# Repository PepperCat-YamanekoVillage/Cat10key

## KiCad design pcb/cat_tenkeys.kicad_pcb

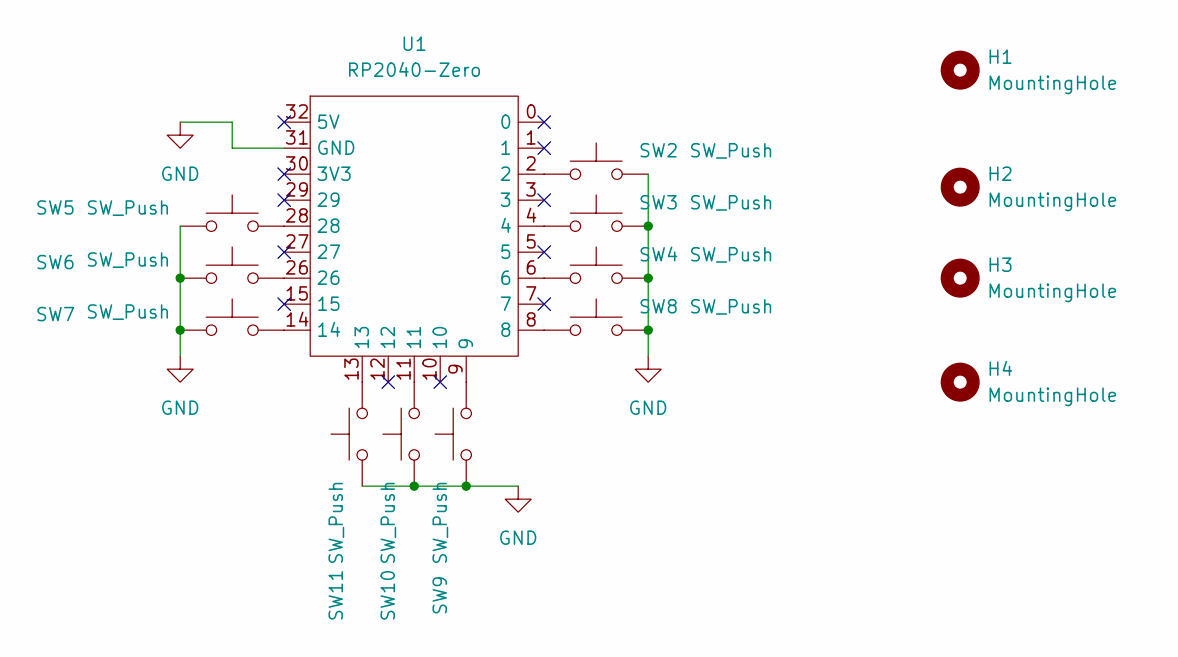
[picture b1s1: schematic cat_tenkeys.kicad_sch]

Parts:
H1, H2, H3, H4: MountingHole; MountingHole_3.2mm_M3
SW2, SW3, SW4, SW5, SW6, SW7, SW8, SW9, SW10, SW11: SW_Push; Switch_1u
U1: RP2040-Zero; RP2040-Zero-THT

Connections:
GND: SW2.2, SW3.2, SW4.2, SW5.1, SW6.1, SW7.1, SW8.2, SW9.1, SW10.1, SW11.1, U1.31 (GND)
unnamed: SW2.1, U1.2
unnamed: SW3.1, U1.4
unnamed: SW4.1, U1.6
unnamed: SW5.2, U1.28
unnamed: SW6.2, U1.26
unnamed: SW7.2, U1.14
unnamed: SW8.1, U1.8
unnamed: SW9.2, U1.9
unnamed: SW10.2, U1.11
unnamed: SW11.2, U1.13

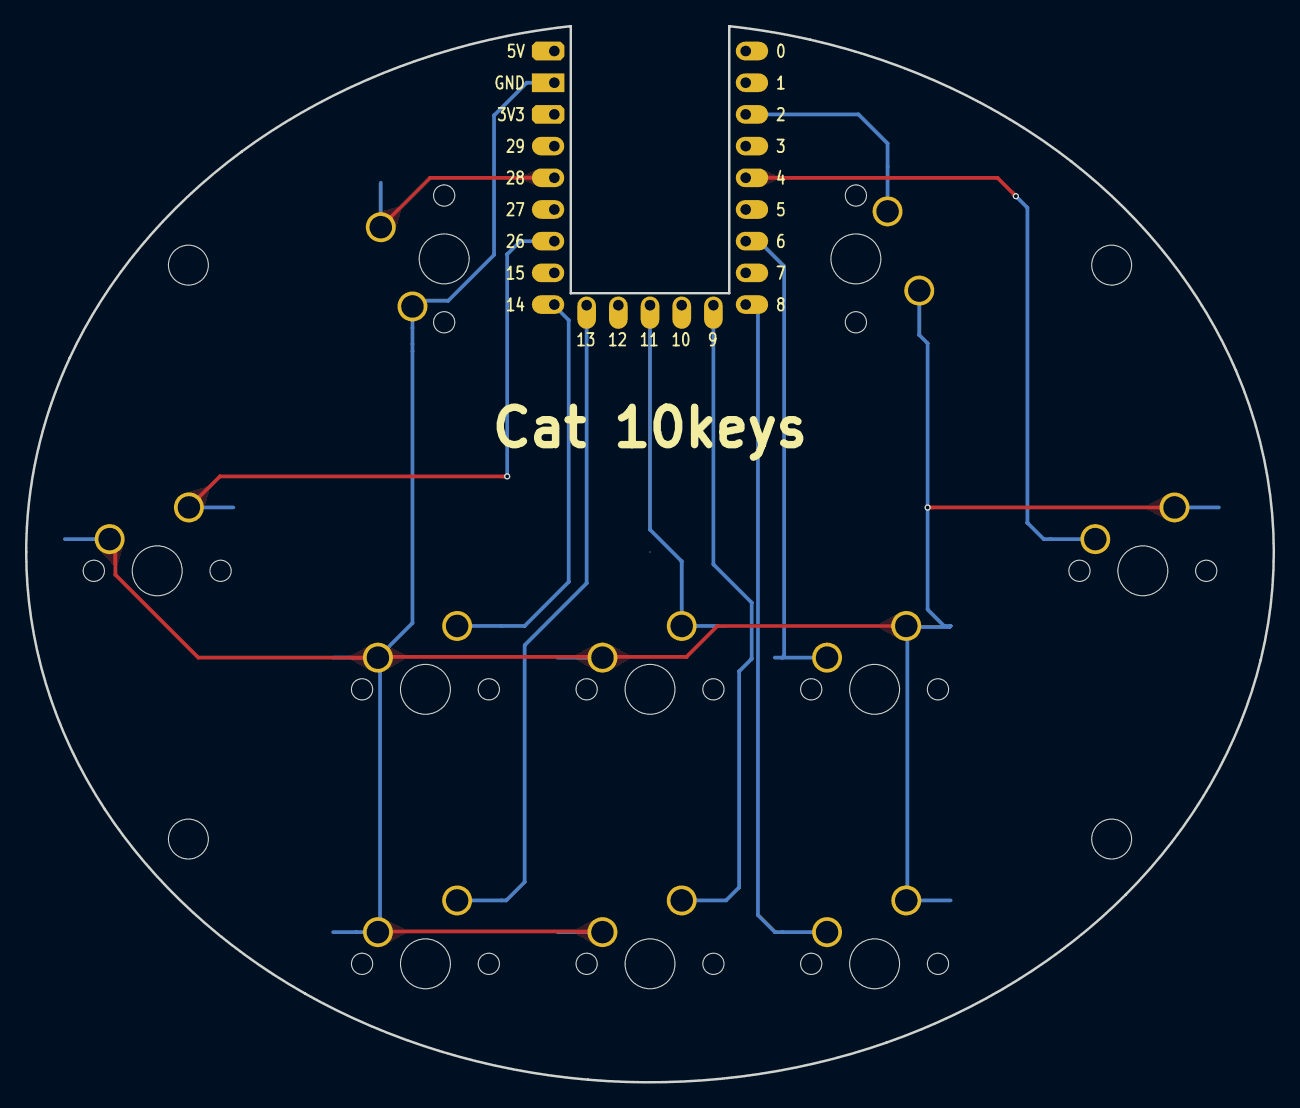
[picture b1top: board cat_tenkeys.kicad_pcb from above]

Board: 2 copper layers, 100.0 x 84.6 mm, 15 parts (0 on the bottom side), 11 nets.

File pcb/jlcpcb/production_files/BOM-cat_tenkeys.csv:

Comment,Designator,Footprint,LCSC,Quantity
SW_Push,SW5,Switch_1u,,1
SW_Push,SW11,Switch_1u,,1
SW_Push,SW3,Switch_1u,,1
SW_Push,SW8,Switch_1u,,1
SW_Push,SW10,Switch_1u,,1
SW_Push,SW7,Switch_1u,,1
SW_Push,SW4,Switch_1u,,1
SW_Push,SW2,Switch_1u,,1
RP2040-Zero,U1,RP2040-Zero-THT,,1
SW_Push,SW9,Switch_1u,,1
SW_Push,SW6,Switch_1u,,1

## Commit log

2026-03-02 FIX サンプルキーマップにおいて、数字がLINUXだと認識されなかったので修正
2026-03-02 Create LICENSE
2026-03-02 Update LICENSE
